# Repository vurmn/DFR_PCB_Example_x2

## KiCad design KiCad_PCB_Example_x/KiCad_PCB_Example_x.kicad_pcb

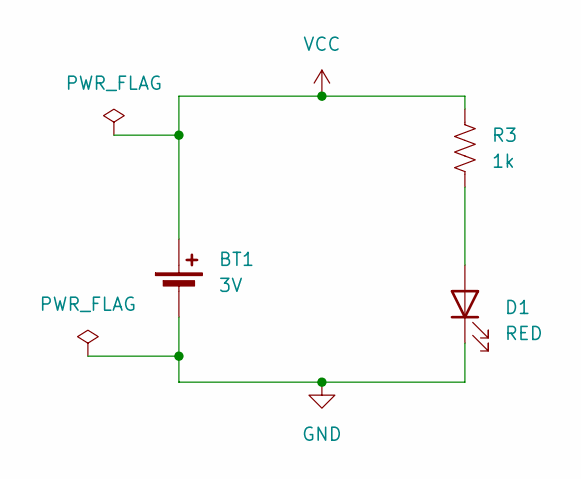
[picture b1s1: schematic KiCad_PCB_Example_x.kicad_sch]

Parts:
BT1: 3V; BatteryHolder_Keystone_1058_1x2032
D1: RED; LED_D5.0mm
R3: 1k; R_Axial_DIN0309_L9.0mm_D3.2mm_P12.70mm_Horizontal

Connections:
GND: BT1.2 (-), D1.1 (K)
unnamed: D1.2 (A), R3.2
VCC: BT1.1 (+), R3.1

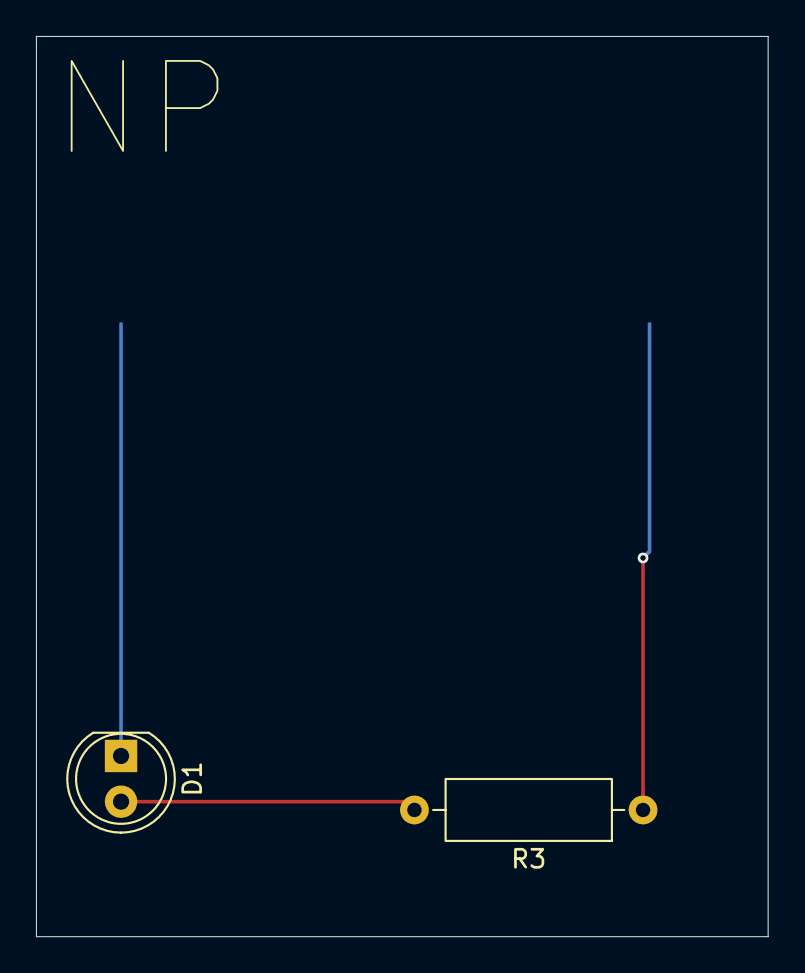
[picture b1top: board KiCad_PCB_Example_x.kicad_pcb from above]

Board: 2 copper layers, 40.6 x 50.0 mm, 3 parts (1 on the bottom side), 3 nets.

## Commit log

2026-03-26 Onboarding
2026-03-26 adding resistors
2026-04-02 KiCad PDB
2026-04-02 Part 3
2026-04-02 Part 3 Complete
2026-04-02 Added Initial
2026-04-02 organization
